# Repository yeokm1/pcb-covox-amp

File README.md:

# pcb-covox-amp
A tiny sound card based on the Covox Speech Thing design which includes an LM386 amplifier. I have another design that just has the resistor ladder portion only without the amplifier which can be found [here](https://github.com/yeokm1/pcb-covox).

##PCB Design software and addons used

1. Kicad 4.0.2 or later

## Video

Due to copyright problems in the music used, this video can only be viewed on a PC. It is blocked on mobile devices and other platforms.

## Images

The picture is of the Rev 2 version with the bug in the limited parallel port grounding. This has been corrected in the Rev 3 gerber but not fabricated.

##Schematic drawings

## Parts required
Use Libreoffice to open [pcb-covox-amp-bom.ods](pcb-covox-amp-bom.ods)

## Errata

As reported in this [issue](https://github.com/yeokm1/pcb-covox-amp/issues/2), there is a mistake in components R2 and C6. As I'm not currently using this project, I'll not be correcting this error.

## References
1. [Hardware implementation references](https://blog.frantovo.cz/c/307/DAC%20%28zvukov%C3%A1%20karta%29%20pro%20LPT%20port%20a.k.a.%20Covox)
2. [Design reference](http://kb.gr8bit.ru/KB0010/GR8BIT-KB0010-Adding-multimedia-capability-covox-device.html)
3. [MJ-2135 package referenced from coqui-dip](https://github.com/open-eie/coqui-dip)
4. [Amplifier circuit](http://www.circuitbasics.com/build-a-great-sounding-audio-amplifier-with-bass-boost-from-the-lm386/)

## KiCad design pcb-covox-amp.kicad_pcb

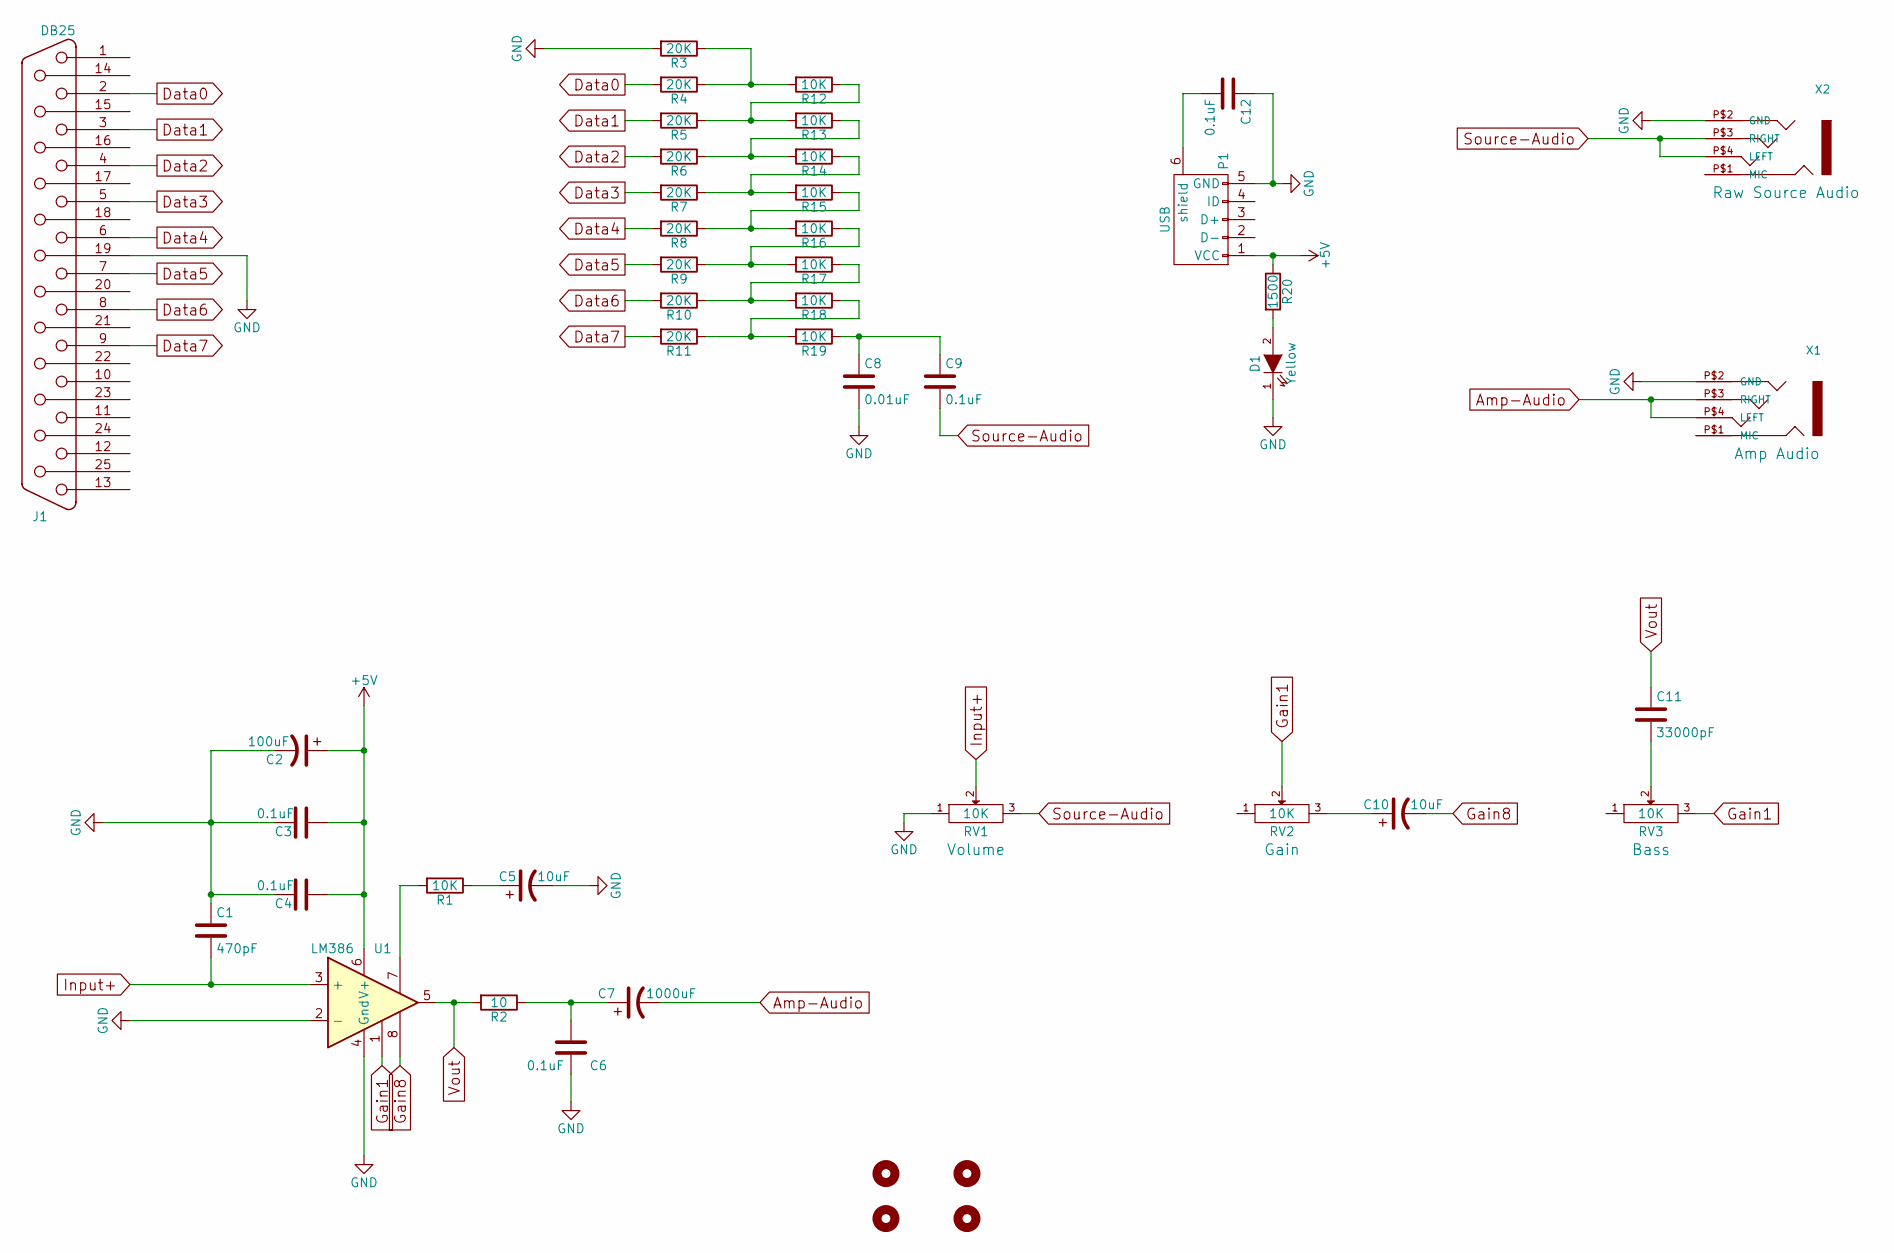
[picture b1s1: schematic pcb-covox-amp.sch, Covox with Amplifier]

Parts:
C1: 470pF; C_0805_HandSoldering
C2: 100uF; c_elec_10x10.5
C3, C4, C6, C9, C12: 0.1uF; C_0805_HandSoldering
C5, C10: 10uF; c_elec_4x5.3
C7: 1000uF; c_elec_10x10.5
C8: 0.01uF; C_0805_HandSoldering
C11: 33000pF; C_0805_HandSoldering
D1: Yellow; LED_0805
J1: DB25; DB25MC
MH1, MH2, MH3, MH4: MOUNTHOLE; MountingHole_3.2mm_M3_ISO14580_Pad
P1: USB; USB_Micro-B
R1, R12, R13, R14, R15, R16, R17, R18, R19: 10K; R_0805_HandSoldering
R2: 10; R_0805_HandSoldering
R3, R4, R5, R6, R7, R8, R9, R10, R11: 20K; R_0805_HandSoldering
R20: 1500; R_0805_HandSoldering
RV1, RV2, RV3: 10K; Potentiometer_Alps-RK163-single_15mm
U1: LM386; SOIC-8_3.9x4.9mm_Pitch1.27mm
X1: Amp; mj-2135-MJ-2135
X2: Raw; mj-2135-MJ-2135

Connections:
+5V: C2.1, C3.1, C4.1, P1.1 (VCC), R20.1, U1.6 (V+)
Amp-Audio: C7.2, X1.P$3 (RIGHT), X1.P$4 (LEFT), X1.P$5 (LEFT)
Data0: J1.2, R4.2
Data1: J1.3, R5.2
Data2: J1.4, R6.2
Data3: J1.5, R7.2
Data4: J1.6, R8.2
Data5: J1.7, R9.2
Data6: J1.8, R10.2
Data7: J1.9, R11.2
GND: C1.1, C2.2, C3.2, C4.2, C5.2, C6.2, C8.2, C12.1, D1.1 (K), J1.19, P1.5 (GND), R3.2, RV1.1, U1.2 (-), U1.4 (Gnd), X1.P$2 (GND), X2.P$2 (GND)
Gain1: RV2.2, RV3.3, U1.1
Gain8: C10.2, U1.8
Input+: C1.2, RV1.2, U1.3 (+)
unnamed: C5.1, R1.1
unnamed: C6.1, C7.1, R2.1
unnamed: C8.1, C9.1, R19.1
unnamed: C10.1, RV2.3
unnamed: C11.2, RV3.2
unnamed: C12.2, P1.6 (shield)
unnamed: D1.2 (A), R20.2
unnamed: R1.2, U1.7
unnamed: R10.1, R17.1, R18.2
unnamed: R11.1, R18.1, R19.2
unnamed: R5.1, R12.1, R13.2
unnamed: R3.1, R4.1, R12.2
unnamed: R6.1, R13.1, R14.2
unnamed: R7.1, R14.1, R15.2
unnamed: R8.1, R15.1, R16.2
unnamed: R9.1, R16.1, R17.2
Source-Audio: C9.2, RV1.3, X2.P$3 (RIGHT), X2.P$4 (LEFT), X2.P$5 (LEFT)
Vout: C11.1, R2.2, U1.5

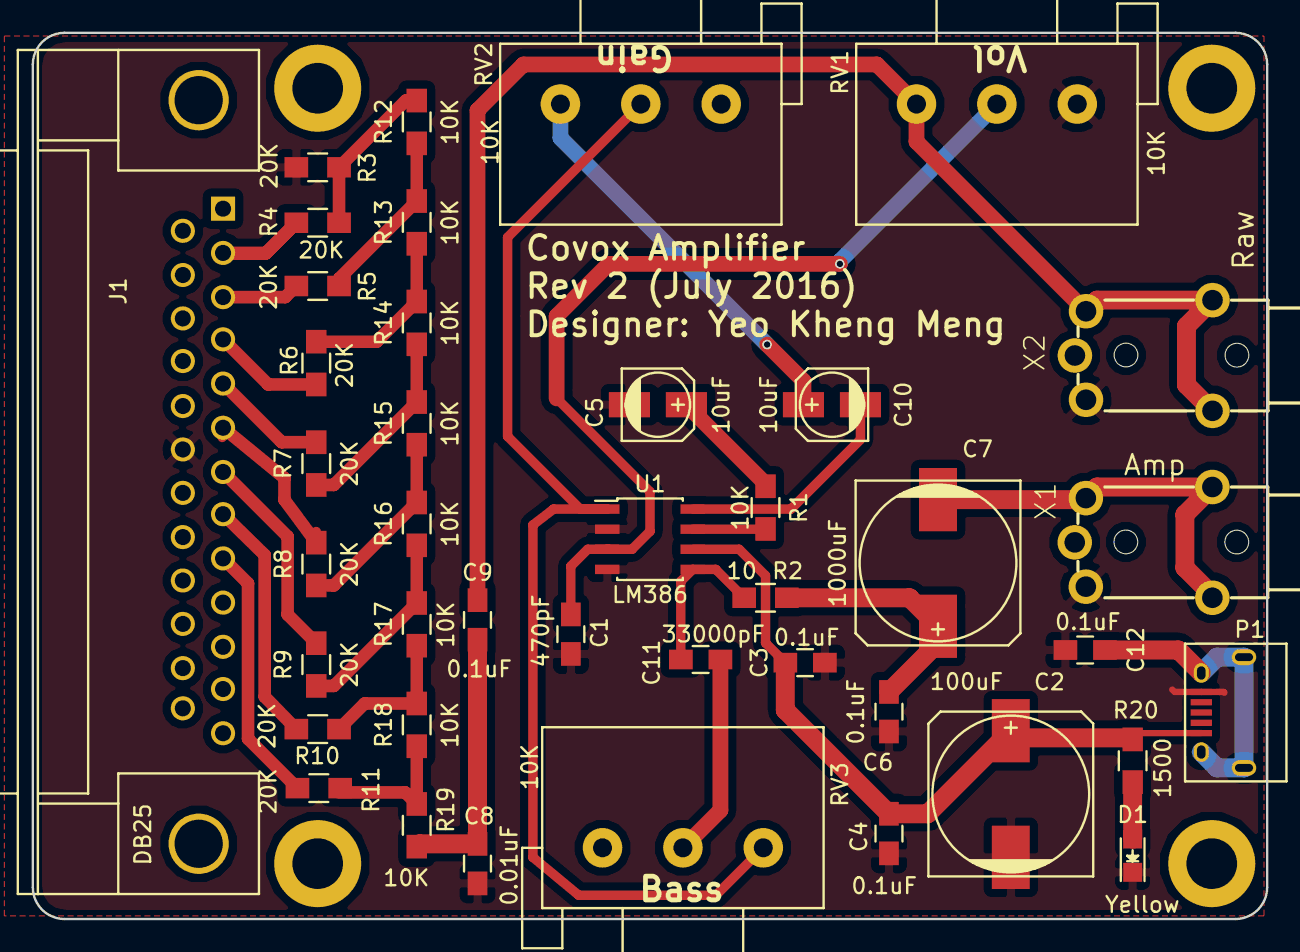
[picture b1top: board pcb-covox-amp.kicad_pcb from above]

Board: 2 copper layers, 78.0 x 56.0 mm, 45 parts (0 on the bottom side), 32 nets.

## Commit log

2016-07-02 initial
2016-07-02 another commit
2016-07-02 remove
2016-07-02 curve corners
2016-07-02 silkscreen details
2016-07-02 add gitignore
2016-07-02 gerber
2016-07-02 rev 1 gerber
2016-07-03 add mounting holes rev 2
2016-07-10 some update
2016-07-11 some adjustments
2016-07-11 update db25 package
2016-07-11 rev2 gerber
2016-07-13 adjust foot print
2016-07-13 adjust add pot direction
2016-07-13 rev 2 gerber
2016-07-20 add image
2016-07-20 add license
2016-07-20 images
2016-07-20 rename
2016-07-22 adjust package size for 10uF capacitor
2016-07-24 assign all parallel pout ground pins and rev 3
2016-07-24 gitignore
2016-07-24 rev3
2017-01-02 higher res schematic image
2023-08-22 add errata
2023-12-11 Add a 3D model for covox amp
    it's poor but usable.
